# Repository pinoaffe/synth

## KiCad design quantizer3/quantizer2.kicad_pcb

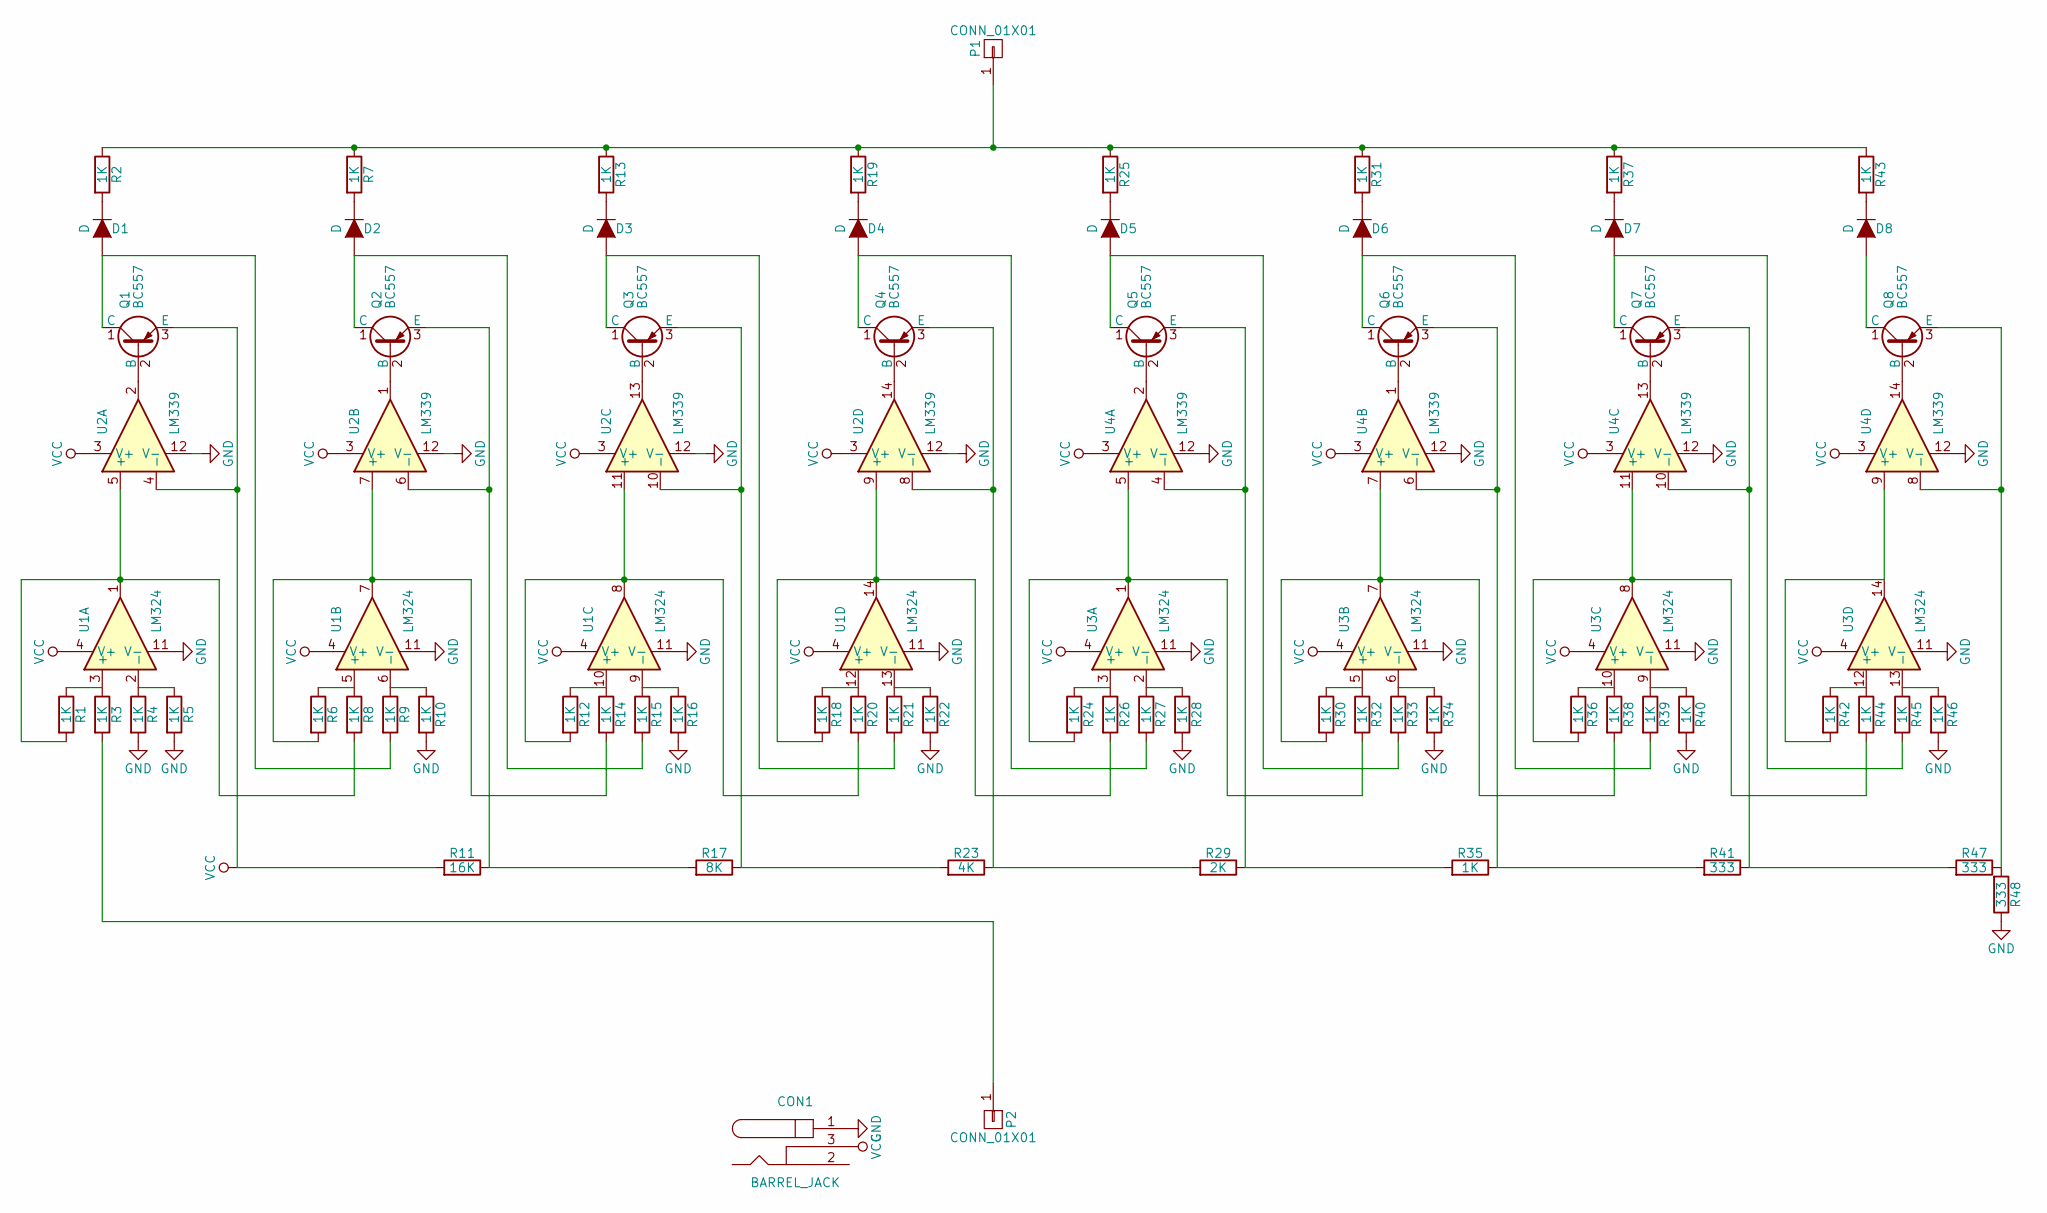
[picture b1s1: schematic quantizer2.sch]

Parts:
CON1: BARREL_JACK; Pin_Header_Straight_1x03_Pitch2.54mm
D1, D2, D3, D4, D5, D6, D7, D8: D; D_DO-15_P10.16mm_Horizontal
P1, P2: CONN_01X01; Pin_Header_Straight_1x01_Pitch2.54mm
Q1, Q2, Q3, Q4, Q5, Q6, Q7, Q8: BC557; TO-92_Inline_Narrow_Oval
R1, R2, R3, R4, R5, R6, R7, R8, R9, R10, R12, R13, R14, R15, R16, R18, R19, R20, R21, R22, R24, R25, R26, R27, R28, R30, R31, R32, R33, R34, R35, R36, R37, R38, R39, R40, R42, R43, R44, R45, R46: 1K; R_Axial_DIN0207_L6.3mm_D2.5mm_P10.16mm_Horizontal
R11: 16K; R_Axial_DIN0207_L6.3mm_D2.5mm_P10.16mm_Horizontal
R17: 8K; R_Axial_DIN0207_L6.3mm_D2.5mm_P10.16mm_Horizontal
R23: 4K; R_Axial_DIN0207_L6.3mm_D2.5mm_P10.16mm_Horizontal
R29: 2K; R_Axial_DIN0207_L6.3mm_D2.5mm_P10.16mm_Horizontal
R41, R47, R48: 333; R_Axial_DIN0207_L6.3mm_D2.5mm_P10.16mm_Horizontal
U1, U3: LM324; DIP-14_W7.62mm_LongPads
U2, U4: LM339; DIP-14_W7.62mm_LongPads

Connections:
GND: CON1.1, R4.2, R5.2, R10.2, R16.2, R22.2, R28.2, R34.2, R40.2, R46.2, R48.1, U1.11 (V-), U2.12 (V-), U3.11 (V-), U4.12 (V-)
unnamed: D1.1 (K), R2.2
unnamed: D1.2 (A), Q1.1 (C), R9.2
unnamed: D2.1 (K), R7.2
unnamed: D2.2 (A), Q2.1 (C), R15.2
unnamed: D3.1 (K), R13.2
unnamed: D3.2 (A), Q3.1 (C), R21.2
unnamed: D4.1 (K), R19.2
unnamed: D4.2 (A), Q4.1 (C), R27.2
unnamed: D5.1 (K), R25.2
unnamed: D5.2 (A), Q5.1 (C), R33.2
unnamed: D6.1 (K), R31.2
unnamed: D6.2 (A), Q6.1 (C), R39.2
unnamed: D7.1 (K), R37.2
unnamed: D7.2 (A), Q7.1 (C), R45.2
unnamed: D8.1 (K), R43.2
unnamed: D8.2 (A), Q8.1 (C)
unnamed: P1.1, R2.1, R7.1, R13.1, R19.1, R25.1, R31.1, R37.1, R43.1
unnamed: P2.1, R3.2
unnamed: Q1.2 (B), U2.2
unnamed: Q2.2 (B), U2.1
unnamed: Q2.3 (E), R11.1, R17.2, U2.6 (-)
unnamed: Q3.2 (B), U2.13
unnamed: Q3.3 (E), R17.1, R23.2, U2.10 (-)
unnamed: Q4.2 (B), U2.14
unnamed: Q4.3 (E), R23.1, R29.2, U2.8 (-)
unnamed: Q5.2 (B), U4.2
unnamed: Q5.3 (E), R29.1, R35.2, U4.4 (-)
unnamed: Q6.2 (B), U4.1
unnamed: Q6.3 (E), R35.1, R41.2, U4.6 (-)
unnamed: Q7.2 (B), U4.13
unnamed: Q7.3 (E), R41.1, R47.2, U4.10 (-)
unnamed: Q8.2 (B), U4.14
unnamed: Q8.3 (E), R47.1, R48.2, U4.8 (-)
unnamed: R1.1, R3.1, U1.3 (+)
unnamed: R1.2, R8.2, U1.1, U2.5 (+)
unnamed: R4.1, R5.1, U1.2 (-)
unnamed: R6.1, R8.1, U1.5 (+)
unnamed: R9.1, R10.1, U1.6 (-)
unnamed: R12.1, R14.1, U1.10 (+)
unnamed: R12.2, R20.2, U1.8, U2.11 (+)
unnamed: R6.2, R14.2, U1.7, U2.7 (+)
unnamed: R15.1, R16.1, U1.9 (-)
unnamed: R18.1, R20.1, U1.12 (+)
unnamed: R18.2, R26.2, U1.14, U2.9 (+)
unnamed: R21.1, R22.1, U1.13 (-)
unnamed: R24.1, R26.1, U3.3 (+)
unnamed: R24.2, R32.2, U3.1, U4.5 (+)
unnamed: R27.1, R28.1, U3.2 (-)
unnamed: R30.1, R32.1, U3.5 (+)
unnamed: R30.2, R38.2, U3.7, U4.7 (+)
unnamed: R33.1, R34.1, U3.6 (-)
unnamed: R36.1, R38.1, U3.10 (+)
unnamed: R36.2, R44.2, U3.8, U4.11 (+)
unnamed: R39.1, R40.1, U3.9 (-)
unnamed: R42.1, R44.1, U3.12 (+)
unnamed: R42.2, U3.14, U4.9 (+)
unnamed: R45.1, R46.1, U3.13 (-)
VCC: CON1.3, Q1.3 (E), R11.2, U1.4 (V+), U2.3 (V+), U2.4 (-), U3.4 (V+), U4.3 (V+)

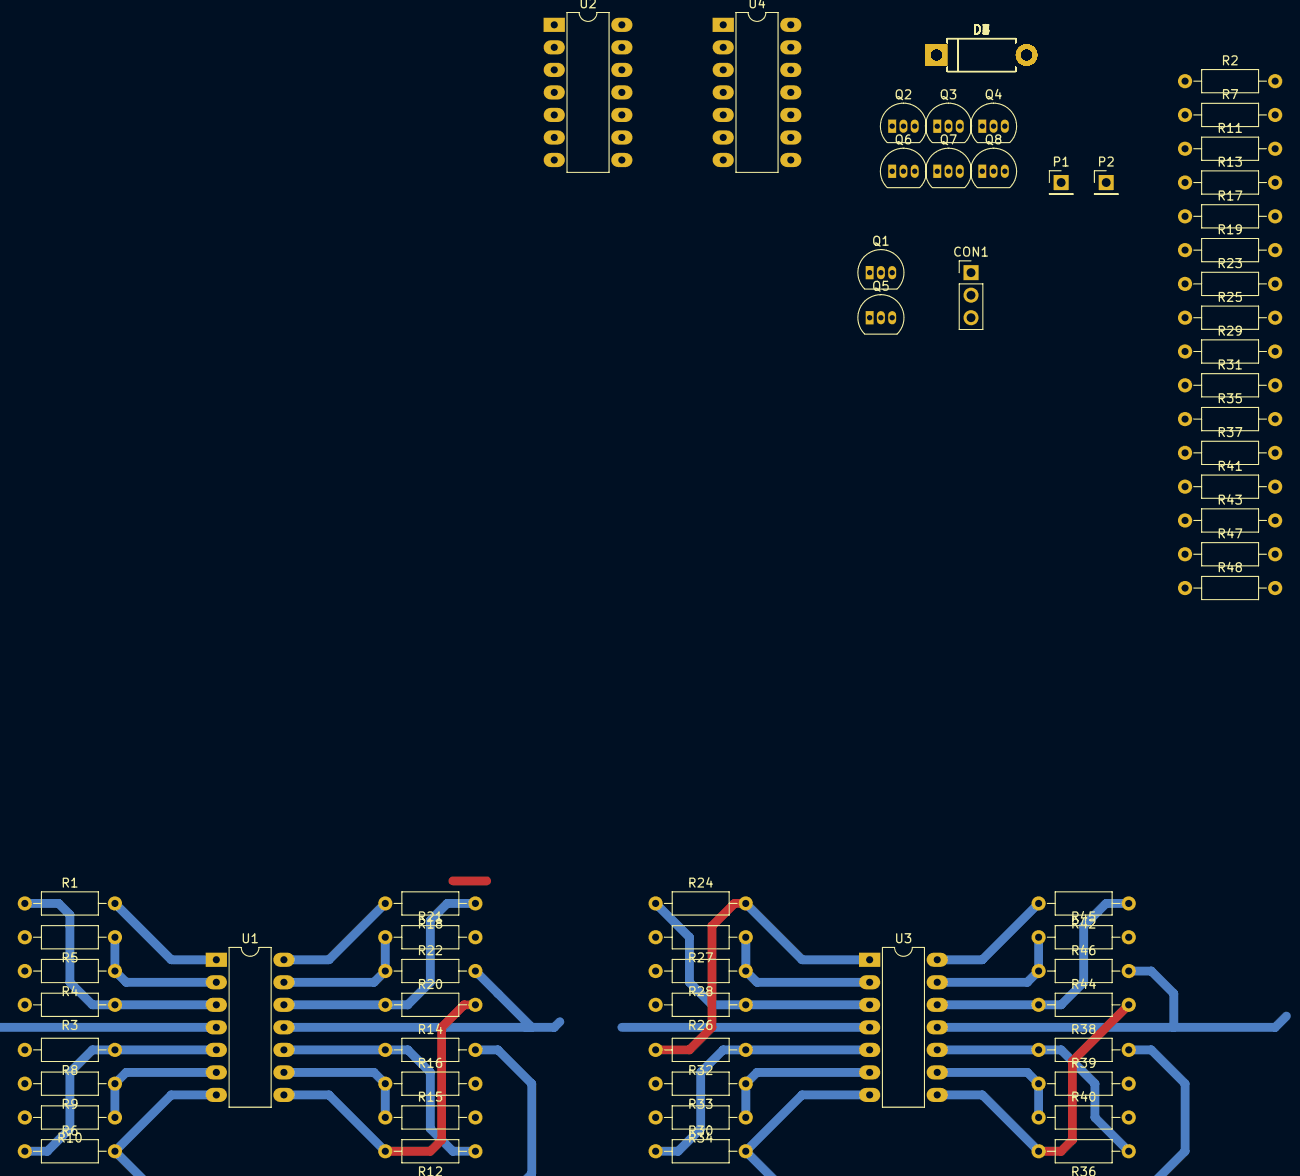
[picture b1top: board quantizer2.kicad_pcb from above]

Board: 2 copper layers, 71 parts (0 on the bottom side), 59 nets.

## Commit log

2017-10-17 added empty faceplate
2017-10-17 added power, 2n3904 vco
